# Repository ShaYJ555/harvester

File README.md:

# 简介
> 本项目是胡萝卜收割机的电控部分内容主要包含以下内容
- 硬件
- 软件
- 资料

# 硬件
**使用两个esp32配合5颗drv8825来实现功能控制**

# 软件
> slaveboard&masterboard之间通过硬件串口2通信
## slaveboard
> 用于控制机器底盘的运动。
## masterboard
> 用于控制机器步进电机和舵机的运动。

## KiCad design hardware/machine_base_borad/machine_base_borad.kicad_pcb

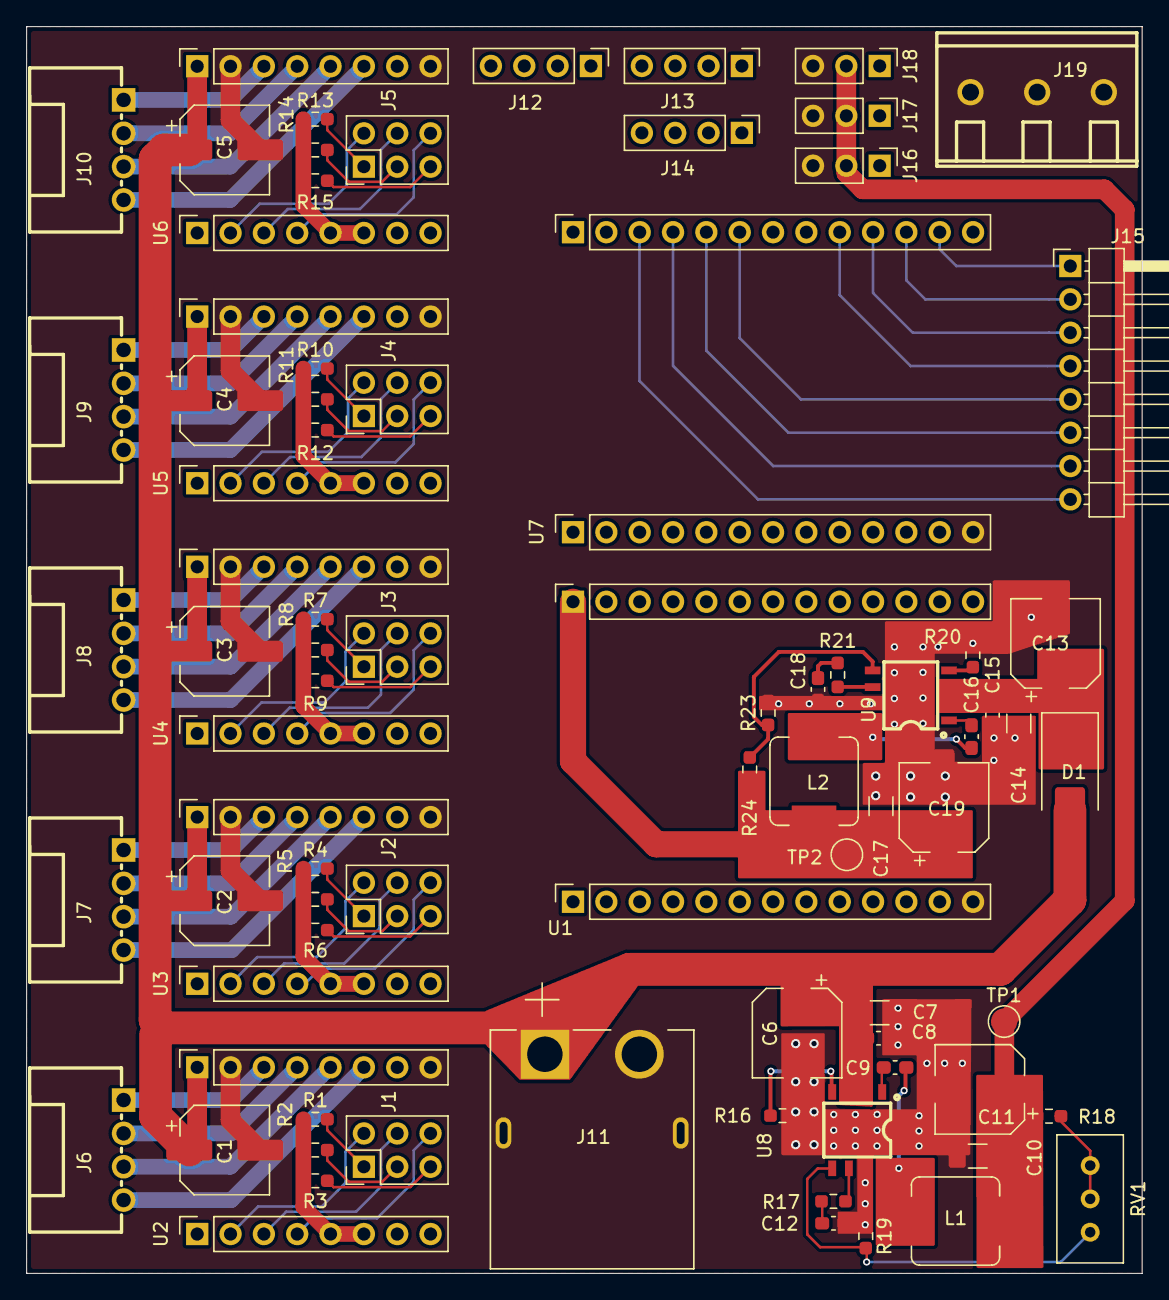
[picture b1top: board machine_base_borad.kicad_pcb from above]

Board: 4 copper layers, 85.0 x 95.0 mm, 76 parts (0 on the bottom side), 103 nets.

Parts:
C1, C2, C3, C4, C5: C_Polarized_Small; CP_Elec_6.3x7.7
C6, C11, C13, C19: 220uf; CP_Elec_6.3x7.7
C7, C14: 4.7uf; C_1206_3216Metric_Pad1.33x1.80mm_HandSolder
C8, C9, C15, C16: 100nf; C_0603_1608Metric_Pad1.08x0.95mm_HandSolder
C10, C17: 47uf; C_1206_3216Metric_Pad1.33x1.80mm_HandSolder
C12, C18: 4.7nf; C_0603_1608Metric_Pad1.08x0.95mm_HandSolder
D1: SS54; D_SMB_Handsoldering
J1, J2, J3, J4, J5: Conn_02x03_Odd_Even; PinHeader_2x03_P2.54mm_Vertical
J6, J7, J8, J9, J10: Conn_01x04; CONN-TH_4P-P2.54-XH2.54-WO-4P
J11: XT60PW-M; AMASS_XT60PW-M
J12, J13, J14: Conn_01x04; PinHeader_1x04_P2.54mm_Vertical
J15: Conn_01x08; PinHeader_1x08_P2.54mm_Horizontal
J16, J17, J18: Conn_01x03; PinHeader_1x03_P2.54mm_Vertical
J19: Conn_01x03; CONN-TH_3P-P5.00_WJ500V-5.08-3P
L1, L2: 4.7uH; L_Sumida_CDMC6D28_7.25x6.5mm
R1, R2, R3, R4, R5, R6, R7, R8, R9, R10, R11, R12, R13, R14, R15: 10k; R_0603_1608Metric_Pad0.98x0.95mm_HandSolder
R16, R20: 200k; R_0603_1608Metric_Pad0.98x0.95mm_HandSolder
R17, R21: 20k; R_0603_1608Metric_Pad0.98x0.95mm_HandSolder
R18: 15k; R_0603_1608Metric_Pad0.98x0.95mm_HandSolder
R19: 3.3k; R_0603_1608Metric_Pad0.98x0.95mm_HandSolder
R23: 10.2k; R_0603_1608Metric_Pad0.98x0.95mm_HandSolder
R24: 31.6k; R_0603_1608Metric_Pad0.98x0.95mm_HandSolder
RV1: 10k; Potentiometer_Bourns_3296W_Vertical
TP1, TP2: TestPoint; TestPoint_Pad_D2.0mm
U1, U7: esp_module
U2: stepper1; stepper_motor
U3: stepper2; stepper_motor
U4: stepper3; stepper_motor
U5: stepper4; stepper_motor
U6: stepper5; stepper_motor
U8, U9: std:5f48b54a4a9c4b9abe6e863ac7419a9f; SCT2450

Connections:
/ESP_RX2: U1.19 (GPIO16), U7.20 (GPIO17)
/ESP_TX2: U1.20 (GPIO17), U7.19 (GPIO16)
/MOTOR1_IN1: J12.4, U1.25 (GPIO22)
/MOTOR1_IN2: J12.3, U1.24 (GPIO19)
/MOTOR2_IN1: J12.2, U1.23 (GPIO23)
/MOTOR2_IN2: J12.1, U1.22 (GPIO18)
/MOTOR3_IN1: J15.1, U7.15 (GPIO15)
/MOTOR3_IN2: J15.2, U7.16 (GPIO02)
/MOTOR4_IN1: J15.3, U7.17 (GPIO00)
/MOTOR4_IN2: J15.4, U7.18 (GPIO04)
/MOTOR5_IN1: J15.5, U7.21 (GPIO05)
/MOTOR5_IN2: J15.6, U7.22 (GPIO18)
/MOTOR6_IN1: J15.7, U7.23 (GPIO23)
/MOTOR6_IN2: J15.8, U7.24 (GPIO19)
/MOTOR7_IN1: J13.1, U7.9 (GPIO26)
/MOTOR7_IN2: J13.2, U7.8 (GPIO25)
/MOTOR8_IN1: J13.3, U7.7 (GPIO33)
/MOTOR8_IN2: J13.4, U7.6 (GPIO32)
/MOTOR9_IN1: J14.4, U7.10 (GPIO27)
/MOTOR9_IN2: J14.3, U7.11 (GPIO14)
/MOTOR10_IN1: J14.2, U7.12 (GPIO12)
/MOTOR10_IN2: J14.1, U7.14 (GPIO13)
/servo1: J16.1, U1.14 (GPIO13)
/servo2: J17.1, U1.15 (GPIO15)
/servo3: J18.1, U1.12 (GPIO12)
/stepper1_A1: J6.3, U2.12 (A1)
/stepper1_A2: J6.4, U2.11 (A2)
/stepper1_B1: J6.2, U2.13 (B1)
/stepper1_B2: J6.1, U2.14 (B2)
/stepper1_DIR: U1.9 (GPIO26), U2.8 (DIR)
/stepper1_STEP: U1.8 (GPIO25), U2.7 (STEP)
/stepper2_A1: J7.3, U3.12 (A1)
/stepper2_A2: J7.4, U3.11 (A2)
/stepper2_B1: J7.2, U3.13 (B1)
/stepper2_B2: J7.1, U3.14 (B2)
/stepper2_DIR: U1.6 (GPIO32), U3.8 (DIR)
/stepper2_STEP: U1.7 (GPIO33), U3.7 (STEP)
/stepper3_A1: J8.3, U4.12 (A1)
/stepper3_A2: J8.4, U4.11 (A2)
/stepper3_B1: J8.2, U4.13 (B1)
/stepper3_B2: J8.1, U4.14 (B2)
/stepper3_DIR: U1.11 (GPIO14), U4.8 (DIR)
/stepper3_STEP: U1.10 (GPIO27), U4.7 (STEP)
/stepper4_A1: J9.3, U5.12 (A1)
/stepper4_A2: J9.4, U5.11 (A2)
/stepper4_B1: J9.2, U5.13 (B1)
/stepper4_B2: J9.1, U5.14 (B2)
/stepper4_DIR: U1.17 (GPIO00), U5.8 (DIR)
/stepper4_STEP: U1.16 (GPIO02), U5.7 (STEP)
/stepper5_A1: J10.3, U6.12 (A1)
/stepper5_A2: J10.4, U6.11 (A2)
/stepper5_B1: J10.2, U6.13 (B1)
/stepper5_B2: J10.1, U6.14 (B2)
/stepper5_DIR: U1.21 (GPIO05), U6.8 (DIR)
/stepper5_STEP: U1.18 (GPIO04), U6.7 (STEP)
GND: C1.2, C2.2, C3.2, C4.2, C5.2, C6.2, C7.2, C8.2, C10.2, C11.2, C12.2, C13.2, C14.2, C15.2, C17.2, C18.2, C19.2, J11.2 (-), J11.S1, J11.S2, J16.3, J17.3, J18.3, J19.1, J19.2, J19.3, R16.2, R19.1, R20.2, R23.1, U1.13 (GND), U2.9 (GND), U2.15 (GND), U3.9 (GND), U3.15 (GND), U4.9 (GND), U4.15 (GND), U5.9 (GND), U5.15 (GND), U6.9 (GND), U6.15 (GND), U7.13 (GND), U8.7 (GND), U9.7 (GND)
unnamed: C12.1, R17.2
unnamed: C18.1, R21.2
unnamed: C13.1, C14.1, C15.1, D1.1 (K), U9.2 (VIN), U9.3 (EN)
unnamed: J1.1, R1.2
unnamed: J1.2, U2.2 (M0)
unnamed: J1.3, R2.2
unnamed: J1.4, U2.3 (M1)
unnamed: J1.5, R3.2
unnamed: J1.6, U2.4 (M2)
unnamed: J2.1, R4.2
unnamed: J2.2, U3.2 (M0)
unnamed: J2.3, R5.2
unnamed: J2.4, U3.3 (M1)
unnamed: J2.5, R6.2
unnamed: J2.6, U3.4 (M2)
unnamed: J3.1, R7.2
unnamed: J3.2, U4.2 (M0)
unnamed: J3.3, R8.2
unnamed: J3.4, U4.3 (M1)
unnamed: J3.5, R9.2
unnamed: J3.6, U4.4 (M2)
unnamed: J4.1, R10.2
unnamed: J4.2, U5.2 (M0)
unnamed: J4.3, R11.2
unnamed: J4.4, U5.3 (M1)
unnamed: J4.5, R12.2
unnamed: J4.6, U5.4 (M2)
unnamed: J5.1, R13.2
unnamed: J5.2, U6.2 (M0)
unnamed: J5.3, R14.2
unnamed: J5.4, U6.3 (M1)
unnamed: J5.5, R15.2
unnamed: J5.6, U6.4 (M2)
unnamed: R18.1, RV1.2, RV1.3
unnamed: C9.1, U8.1 (BOOT)
unnamed: R17.1, U8.6 (COMP)
unnamed: R19.2, RV1.1, U8.5 (FB)
unnamed: R16.1, U8.4 (RT/CLK)
unnamed: C9.2, L1.1, U8.8 (SW)
unnamed: C16.1, U9.1 (BOOT)
unnamed: R21.1, U9.6 (COMP)
unnamed: R23.2, R24.1, U9.5 (FB)
unnamed: R20.1, U9.4 (RT/CLK)
unnamed: C16.2, L2.1, U9.8 (SW)
VCC_3V3: C17.1, C19.1, L2.2, R1.1, R2.1, R3.1, R4.1, R5.1, R6.1, R7.1, R8.1, R9.1, R10.1, R11.1, R12.1, R13.1, R14.1, R15.1, R24.2, TP2.1, U1.26 (VIN_3V3), U2.5 (#RST), U2.6 (#SLEEP), U3.5 (#RST), U3.6 (#SLEEP), U4.5 (#RST), U4.6 (#SLEEP), U5.5 (#RST), U5.6 (#SLEEP), U6.5 (#RST), U6.6 (#SLEEP), U7.26 (VIN_3V3)
VCC_Servo: C10.1, C11.1, J16.2, J17.2, J18.2, L1.2, R18.2, TP1.1
VIN: C1.1, C2.1, C3.1, C4.1, C5.1, C6.1, C7.1, C8.1, D1.2 (A), J11.1 (+), U2.16 (VOUT), U3.16 (VOUT), U4.16 (VOUT), U5.16 (VOUT), U6.16 (VOUT), U8.2 (VIN), U8.3 (EN)

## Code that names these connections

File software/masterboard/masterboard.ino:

/*
  前进、后退、左转、右转   四个button
  中间步进电机上升下降     1个button  stepper1
  盒子一出一入            1个        stepper2
  上升下降                1个        stepper3、stepper4
  舵机旋转180             1个     点一下旋转180 再点归位
  传送带                  1个     点一下开，点一下关闭          
*/

#define BLINKER_WIFI

#include <Blinker.h>
#include <stdint.h>
#include <HardwareSerial.h>  // 硬件串口

#define STEPPER1_STEP 25
#define STEPPER1_DIR 26
#define STEPPER2_STEP 33
#define STEPPER2_DIR 32
#define STEPPER3_STEP 27
#define STEPPER3_DIR 14
#define STEPPER4_STEP 2
#define STEPPER4_DIR 0
#define STEPPER5_STEP 4
#define STEPPER5_DIR 5

#define STEPPER1_STEP_CHANNEL 4
#define STEPPER2_STEP_CHANNEL 5
#define STEPPER3_STEP_CHANNEL 6
#define STEPPER4_STEP_CHANNEL 7
#define STEPPER5_STEP_CHANNEL 8

#define STEPPER_PWM_FREQ       1000
#define STEPPER_PWM_RESOLUTION 8

#define MOTOR1_IN1 22
#define MOTOR1_IN2 19
#define MOTOR2_IN1 23
#define MOTOR2_IN2 18

#define MOTOR1_IN1_CHANNEL 0
#define MOTOR1_IN2_CHANNEL 1
#define MOTOR2_IN1_CHANNEL 2
#define MOTOR2_IN2_CHANNEL 3

#define MOTOR_PWM_FREQ         1000
#define MOTOR_PWM_RESOLUTION   8

#define SERVO1 13

#define SERVO1_CHANNEL     9

#define SERVO2 15
#define SERVO3 12

HardwareSerial SerialPort(2);  // use UART2

char auth[] = "0eb5bbed414b";
char ssid[] = "OnePlus";
char pswd[] = "99999999";

// 底盘运动
BlinkerButton ButtonForward("forward");
BlinkerButton ButtonBackward("backward");
BlinkerButton ButtonLeft("left");
BlinkerButton ButtonRight("right");

// 直流电机运动
BlinkerButton ButtonBelt("belt");  // 皮带

// 步进电机运动
BlinkerButton ButtonCenter("center");    // 中间开沟覆土装置升降
BlinkerButton ButtonBox1("box1");        // 运输箱子
BlinkerButton ButtonLifting("lifting");  // 升降装置

// 开沟覆土舵机
BlinkerButton ButtonCenterServo("servo");  // 开沟覆土舵机

void forward(const String& state);
void backward(const String& state);
void left(const String& state);
void right(const String& state);
void beltrun(const String& state);
void centerservo(const String& state);
void centerstepper(const String& state);
void box1(const String& state);
void lifting(const String& state);

void setup() {
  // put your setup code here, to run once:
  motor_init();
  SerialPort.begin(9600);

  // 初始化串口
  Serial.begin(115200);
  BLINKER_DEBUG.stream(Serial);
  BLINKER_DEBUG.debugAll();

  Blinker.begin(auth, ssid, pswd);
  // 底盘运动
  ButtonForward.attach(forward);
  ButtonBackward.attach(backward);
  ButtonLeft.attach(left);
  ButtonRight.attach(right);
  // 皮带运动
  ButtonBelt.attach(beltrun);
  // 舵机运动
  ButtonCenterServo.attach(centerservo);
  // 步进电机
  ButtonCenter.attach(centerstepper);
  ButtonBox1.attach(box1);
  ButtonLifting.attach(lifting);
}

void loop() {
  // put your main code here, to run repeatedly:
  Blinker.run();
}

void motor_init() {
  //步进电机
  ledcSetup(STEPPER1_STEP_CHANNEL, STEPPER_PWM_FREQ, STEPPER_PWM_RESOLUTION);
  ledcAttachPin(STEPPER1_STEP, STEPPER1_STEP_CHANNEL);
  pinMode(STEPPER1_DIR, OUTPUT);

  ledcSetup(STEPPER2_STEP_CHANNEL, STEPPER_PWM_FREQ, STEPPER_PWM_RESOLUTION);
  ledcAttachPin(STEPPER2_STEP, STEPPER2_STEP_CHANNEL);
  pinMode(STEPPER2_DIR, OUTPUT);

  ledcSetup(STEPPER3_STEP_CHANNEL, STEPPER_PWM_FREQ, STEPPER_PWM_RESOLUTION);
  ledcAttachPin(STEPPER3_STEP, STEPPER3_STEP_CHANNEL);
  pinMode(STEPPER3_DIR, OUTPUT);

  ledcSetup(STEPPER4_STEP_CHANNEL, STEPPER_PWM_FREQ, STEPPER_PWM_RESOLUTION);
  ledcAttachPin(STEPPER4_STEP, STEPPER4_STEP_CHANNEL);
  pinMode(STEPPER4_DIR, OUTPUT);

  ledcSetup(STEPPER5_STEP_CHANNEL, STEPPER_PWM_FREQ, STEPPER_PWM_RESOLUTION);
  ledcAttachPin(STEPPER5_STEP, STEPPER5_STEP_CHANNEL);
  pinMode(STEPPER5_DIR, OUTPUT);
  // 直流电机--皮带
  ledcSetup(MOTOR1_IN1_CHANNEL, MOTOR_PWM_FREQ, MOTOR_PWM_RESOLUTION);
  ledcAttachPin(MOTOR1_IN1, MOTOR1_IN1_CHANNEL);

  ledcSetup(MOTOR1_IN2_CHANNEL, MOTOR_PWM_FREQ, MOTOR_PWM_RESOLUTION);
  ledcAttachPin(MOTOR1_IN2, MOTOR1_IN2_CHANNEL);

  ledcSetup(MOTOR2_IN1_CHANNEL, MOTOR_PWM_FREQ, MOTOR_PWM_RESOLUTION);
  ledcAttachPin(MOTOR2_IN1, MOTOR2_IN1_CHANNEL);

  ledcSetup(MOTOR2_IN2_CHANNEL, MOTOR_PWM_FREQ, MOTOR_PWM_RESOLUTION);
  ledcAttachPin(MOTOR2_IN2, MOTOR2_IN2_CHANNEL);

  ledcSetup(SERVO1_CHANNEL, 50, 10);
  ledcAttachPin(SERVO1, SERVO1_CHANNEL);

  digitalWrite(STEPPER1_DIR,HIGH);
  digitalWrite(STEPPER2_DIR,HIGH);
  digitalWrite(STEPPER3_DIR,HIGH);
  digitalWrite(STEPPER4_DIR,HIGH);
  ledcWrite(SERVO1_CHANNEL,50);    
}

void forward(const String& state) {
  BLINKER_LOG("[forward] >> get button state:", state);
  if (state == BLINKER_CMD_BUTTON_PRESSED) {
    SerialPort.write('F');
  } else if (state == BLINKER_CMD_BUTTON_RELEASED) {
    SerialPort.write('S');
  }
}

void backward(const String& state) {
  BLINKER_LOG("[backward] >> get button state:", state);
  if (state == BLINKER_CMD_BUTTON_PRESSED) {
    SerialPort.write('B');
  } else if (state == BLINKER_CMD_BUTTON_RELEASED) {
    SerialPort.write('S');
  }
}

void left(const String& state) {
  BLINKER_LOG("[left] >> get button state:", state);
  if (state == BLINKER_CMD_BUTTON_PRESSED) {
    SerialPort.write('L');
  } else if (state == BLINKER_CMD_BUTTON_RELEASED) {
    SerialPort.write('S');
  }
}

void right(const String& state) {
  BLINKER_LOG("[right] >> get button state:", state);
  if (state == BLINKER_CMD_BUTTON_PRESSED) {
    SerialPort.write('R');
  } else if (state == BLINKER_CMD_BUTTON_RELEASED) {
    SerialPort.write('S');
  }
}

void beltrun(const String& state) {
  BLINKER_LOG("[beltrun] >> get button state:", state);
  static uint8_t beltrun1_cmd = 0;
  if (state == BLINKER_CMD_BUTTON_TAP) {
    beltrun1_cmd = !beltrun1_cmd;
    if (beltrun1_cmd == 0)  // 停止
    {
      ledcWrite(MOTOR1_IN1_CHANNEL,0);
      ledcWrite(MOTOR1_IN2_CHANNEL,255);
      ledcWrite(MOTOR2_IN1_CHANNEL,255);
      ledcWrite(MOTOR2_IN2_CHANNEL,0);
    } else if (beltrun1_cmd == 1)         // 运动
    {
      ledcWrite(MOTOR1_IN1_CHANNEL,255);
      ledcWrite(MOTOR1_IN2_CHANNEL,0);
      ledcWrite(MOTOR2_IN1_CHANNEL,0);
      ledcWrite(MOTOR2_IN2_CHANNEL,255);
    }
  }
  else if(state == BLINKER_CMD_BUTTON_PRESSED)
  {
    ledcWrite(MOTOR1_IN1_CHANNEL,0);
    ledcWrite(MOTOR1_IN2_CHANNEL,0);
    ledcWrite(MOTOR2_IN1_CHANNEL,0);
    ledcWrite(MOTOR2_IN2_CHANNEL,0);    
  }

}

void centerservo(const String& state) {
  BLINKER_LOG("[centerservo] >> get button state:", state);
  static uint8_t centerservo_cmd = 0;
  if (state == BLINKER_CMD_BUTTON_TAP) {
    centerservo_cmd = !centerservo_cmd;
    if (centerservo_cmd == 0)  // 转回0
    {
      ledcWrite(SERVO1_CHANNEL,50);
    } else if (centerservo_cmd == 1)  // 转180
    {
      ledcWrite(SERVO1_CHANNEL,120);
    }
  }
}

void centerstepper(const String& state) {
  BLINKER_LOG("[centerstepper] >> get button state:", state);
  static uint8_t centerstepper_cmd = 0;
  if (state == BLINKER_CMD_BUTTON_TAP) {
    centerstepper_cmd = !centerstepper_cmd;
    if (centerstepper_cmd == 0)  // 正转
    {
      digitalWrite(STEPPER1_DIR,HIGH);
    } else if (centerstepper_cmd == 1)  // 反转
    {
      digitalWrite(STEPPER1_DIR,LOW);
    }
  } else if (state == BLINKER_CMD_BUTTON_PRESSED)  // 转
  {
    ledcWrite(STEPPER1_STEP_CHANNEL,128);

  } else if (state == BLINKER_CMD_BUTTON_RELEASED)  // 停
  {
    ledcWrite(STEPPER1_STEP_CHANNEL,0);
  }
}

void box1(const String& state) {
  BLINKER_LOG("[box1] >> get button state:", state);
  static uint8_t box1_cmd = 0;
  if (state == BLINKER_CMD_BUTTON_TAP) {
    box1_cmd = !box1_cmd;
    if (box1_cmd == 0)  // 正转
    {
      digitalWrite(STEPPER2_DIR,LOW);
    } else if (box1_cmd == 1)  // 反转
    {
      digitalWrite(STEPPER2_DIR,HIGH);
    }
  } else if (state == BLINKER_CMD_BUTTON_PRESSED)  // 转
  {
    ledcWrite(STEPPER2_STEP_CHANNEL,128);
  } else if (state == BLINKER_CMD_BUTTON_RELEASED)  // 停
  {
    ledcWrite(STEPPER2_STEP_CHANNEL,0);
  }
}

void lifting(const String& state) {
  BLINKER_LOG("[lifting] >> get button state:", state);
  static uint8_t lifting_cmd = 0;
  if (state == BLINKER_CMD_BUTTON_TAP) {
    lifting_cmd = !lifting_cmd;
    if (lifting_cmd == 0)  // 正转
    {
      digitalWrite(STEPPER3_DIR,HIGH);
      digitalWrite(STEPPER4_DIR,HIGH);
    } else if (lifting_cmd == 1)  // 反转
    {
      digitalWrite(STEPPER3_DIR,LOW);
      digitalWrite(STEPPER4_DIR,LOW);
    }
  } else if (state == BLINKER_CMD_BUTTON_PRESSED)  // 转
  {
    ledcWrite(STEPPER3_STEP_CHANNEL,128);
    ledcWrite(STEPPER4_STEP_CHANNEL,128);
  } else if (state == BLINKER_CMD_BUTTON_RELEASED)  // 停
  {
    ledcWrite(STEPPER3_STEP_CHANNEL,0);
    ledcWrite(STEPPER4_STEP_CHANNEL,0);
  }
}

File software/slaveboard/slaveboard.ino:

#include <HardwareSerial.h>   // 硬件串口

#define MOTOR3_IN1  15
#define MOTOR3_IN2  2
#define MOTOR4_IN1  0
#define MOTOR4_IN2  4
#define MOTOR5_IN1  5
#define MOTOR5_IN2  18
#define MOTOR6_IN1  23
#define MOTOR6_IN2  19

#define MOTOR3_IN1_CHANNEL   0
#define MOTOR3_IN2_CHANNEL   1
#define MOTOR4_IN1_CHANNEL   2
#define MOTOR4_IN2_CHANNEL   3
#define MOTOR5_IN1_CHANNEL   4
#define MOTOR5_IN2_CHANNEL   5
#define MOTOR6_IN1_CHANNEL   6
#define MOTOR6_IN2_CHANNEL   7

#define PWM_FREQ        1000
#define PWM_RESOLUTION  8

HardwareSerial SerialPort(2); // use UART2

void motor_init(void);

void backward(void);
void forward(void);
void left(void);
void right(void);
void stop(void);

void setup() {
  // put your setup code here, to run once:
  motor_init();
  SerialPort.begin(9600);
  Serial.begin(9600);

}

void loop() {
  // put your main code here, to run repeatedly:
    // 检查是否有数据可读
  if (SerialPort.available() > 0) {
    // 读取一个字符
    char receivedChar = SerialPort.read();
    // 判断接收到的字符是否为 'F'
    if (receivedChar == 'F') {
      // 执行特定功能
      forward();
    }
    if (receivedChar == 'B') {
      // 执行特定功能
      backward();
    }
    if (receivedChar == 'L') {
      // 执行特定功能
      left();
    }
    if (receivedChar == 'R') {
      // 执行特定功能
      right();
    }      
    if (receivedChar == 'S') {
      // 执行特定功能
      stop();
    }
  }
}

void motor_init()
{
  ledcSetup(MOTOR3_IN1_CHANNEL,PWM_FREQ,PWM_RESOLUTION);
  ledcAttachPin(MOTOR3_IN1,MOTOR3_IN1_CHANNEL);
  ledcSetup(MOTOR3_IN2_CHANNEL,PWM_FREQ,PWM_RESOLUTION);
  ledcAttachPin(MOTOR3_IN2,MOTOR3_IN2_CHANNEL);  

  ledcSetup(MOTOR4_IN1_CHANNEL,PWM_FREQ,PWM_RESOLUTION);
  ledcAttachPin(MOTOR4_IN1,MOTOR4_IN1_CHANNEL);
  ledcSetup(MOTOR4_IN2_CHANNEL,PWM_FREQ,PWM_RESOLUTION);
  ledcAttachPin(MOTOR4_IN2,MOTOR4_IN2_CHANNEL);

  ledcSetup(MOTOR5_IN1_CHANNEL,PWM_FREQ,PWM_RESOLUTION);
  ledcAttachPin(MOTOR5_IN1,MOTOR5_IN1_CHANNEL);
  ledcSetup(MOTOR5_IN2_CHANNEL,PWM_FREQ,PWM_RESOLUTION);
  ledcAttachPin(MOTOR5_IN2,MOTOR5_IN2_CHANNEL);

  ledcSetup(MOTOR6_IN1_CHANNEL,PWM_FREQ,PWM_RESOLUTION);
  ledcAttachPin(MOTOR6_IN1,MOTOR6_IN1_CHANNEL);
  ledcSetup(MOTOR6_IN2_CHANNEL,PWM_FREQ,PWM_RESOLUTION);
  ledcAttachPin(MOTOR6_IN2,MOTOR6_IN2_CHANNEL); 
}

void forward()
{
  ledcWrite(MOTOR3_IN1_CHANNEL,255);    // 左前
  ledcWrite(MOTOR3_IN2_CHANNEL,0);

  ledcWrite(MOTOR4_IN1_CHANNEL,0);    // 右前
  ledcWrite(MOTOR4_IN2_CHANNEL,255);

  ledcWrite(MOTOR5_IN1_CHANNEL,255);    // 左后
  ledcWrite(MOTOR5_IN2_CHANNEL,0);

  ledcWrite(MOTOR6_IN1_CHANNEL,0);    // 右后
  ledcWrite(MOTOR6_IN2_CHANNEL,255);
}

void backward()
{
  ledcWrite(MOTOR3_IN1_CHANNEL,0);    // 左前
  ledcWrite(MOTOR3_IN2_CHANNEL,255);

  ledcWrite(MOTOR4_IN1_CHANNEL,255);    // 右前
  ledcWrite(MOTOR4_IN2_CHANNEL,0);

  ledcWrite(MOTOR5_IN1_CHANNEL,0);    // 左后
  ledcWrite(MOTOR5_IN2_CHANNEL,255);

  ledcWrite(MOTOR6_IN1_CHANNEL,255);    // 右后
  ledcWrite(MOTOR6_IN2_CHANNEL,0);
}

void left()
{
  ledcWrite(MOTOR3_IN1_CHANNEL,0);    // 左前
  ledcWrite(MOTOR3_IN2_CHANNEL,255);

  ledcWrite(MOTOR4_IN1_CHANNEL,0);    // 右前
  ledcWrite(MOTOR4_IN2_CHANNEL,255);

  ledcWrite(MOTOR5_IN1_CHANNEL,0);    // 左后
  ledcWrite(MOTOR5_IN2_CHANNEL,255);

  ledcWrite(MOTOR6_IN1_CHANNEL,0);    // 右后
  ledcWrite(MOTOR6_IN2_CHANNEL,255);  
}

void right()
{
  ledcWrite(MOTOR3_IN1_CHANNEL,255);    // 左前
  ledcWrite(MOTOR3_IN2_CHANNEL,0);

  ledcWrite(MOTOR4_IN1_CHANNEL,255);    // 右前
  ledcWrite(MOTOR4_IN2_CHANNEL,0);

  ledcWrite(MOTOR5_IN1_CHANNEL,255);    // 左后
  ledcWrite(MOTOR5_IN2_CHANNEL,0);

  ledcWrite(MOTOR6_IN1_CHANNEL,255);    // 右后
  ledcWrite(MOTOR6_IN2_CHANNEL,0);  
}

void stop()
{
  ledcWrite(MOTOR3_IN1_CHANNEL,0);    // 左前
  ledcWrite(MOTOR3_IN2_CHANNEL,0);

  ledcWrite(MOTOR4_IN1_CHANNEL,0);    // 右前
  ledcWrite(MOTOR4_IN2_CHANNEL,0);

  ledcWrite(MOTOR5_IN1_CHANNEL,0);    // 左后
  ledcWrite(MOTOR5_IN2_CHANNEL,0);

  ledcWrite(MOTOR6_IN1_CHANNEL,0);    // 右后
  ledcWrite(MOTOR6_IN2_CHANNEL,0);  
}

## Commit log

2024-06-16 harvester
2024-06-16 添加readme文件
2024-06-16 修改readme文件
